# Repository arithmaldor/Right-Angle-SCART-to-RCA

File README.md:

# Copyright and Disclaimer
Copyright: Jacob Proctor 2018

This documentation describes Open Hardware and is licensed under the
CERN OHL v. 1.2.

You may redistribute and modify this documentation under the terms of the
CERN OHL v.1.2. (http://ohwr.org/cernohl). This documentation is distributed
WITHOUT ANY EXPRESS OR IMPLIED WARRANTY, INCLUDING OF
MERCHANTABILITY, SATISFACTORY QUALITY AND FITNESS FOR A
PARTICULAR PURPOSE. Please see the CERN OHL v.1.2 for applicable
conditions

# SCART to RCA Board

Untested, use at your own risk. Will update at a later date with more complete info.

# Parts

Right Angle SCART Connector, various kinds

RCA Connector: PJRAS3X2S01 is available on Mouser and Digikey, but the colors are wrong. Here are the ones I used, a bit cheaper per part:

https://www.ebay.com/itm/QTY-10-6-WAY-PCB-FEMALE-RCA-JACKS-GREEN-YELLOW-BLUE-WHITE-RED-RED-RCA-268N1-14/112220720415?var=null

Mounting hole size is M3, can be used with motherboard standoffs for mounting on MDF or acrylic or something else.

Capacitors and resistors are 0805

LM1881 SOIC8 sync stripper

Molex microusb

SPDT switch

# Version 0.1
This board is untested, designed for use with a case.

# OSHPark
https://oshpark.com/shared_projects/LrkBxQQG

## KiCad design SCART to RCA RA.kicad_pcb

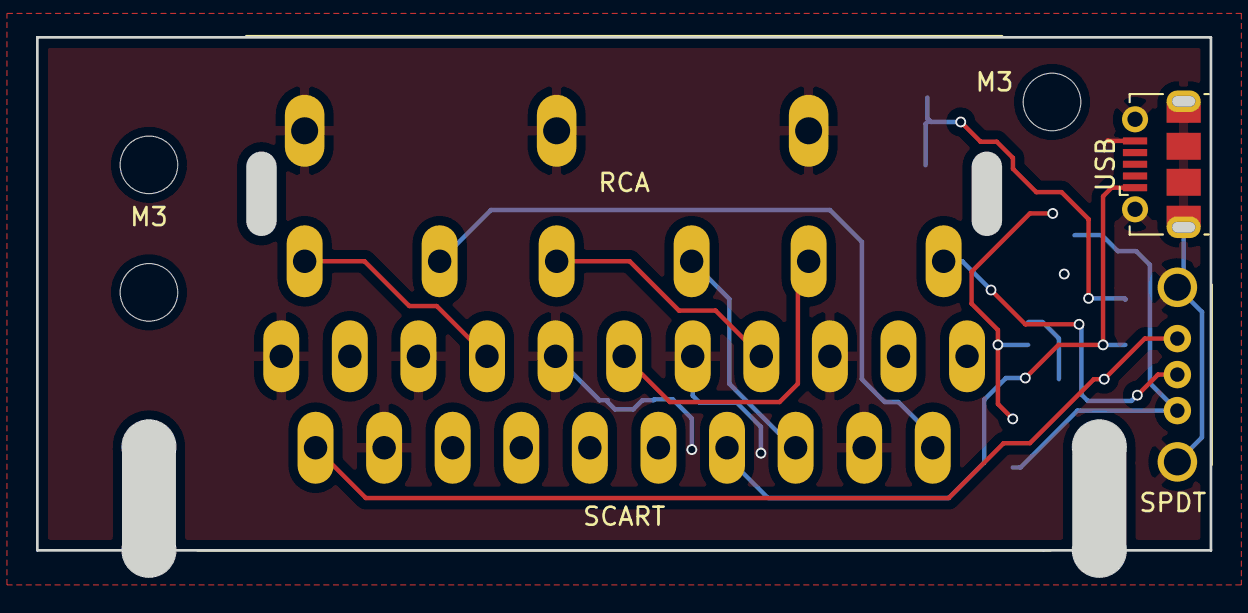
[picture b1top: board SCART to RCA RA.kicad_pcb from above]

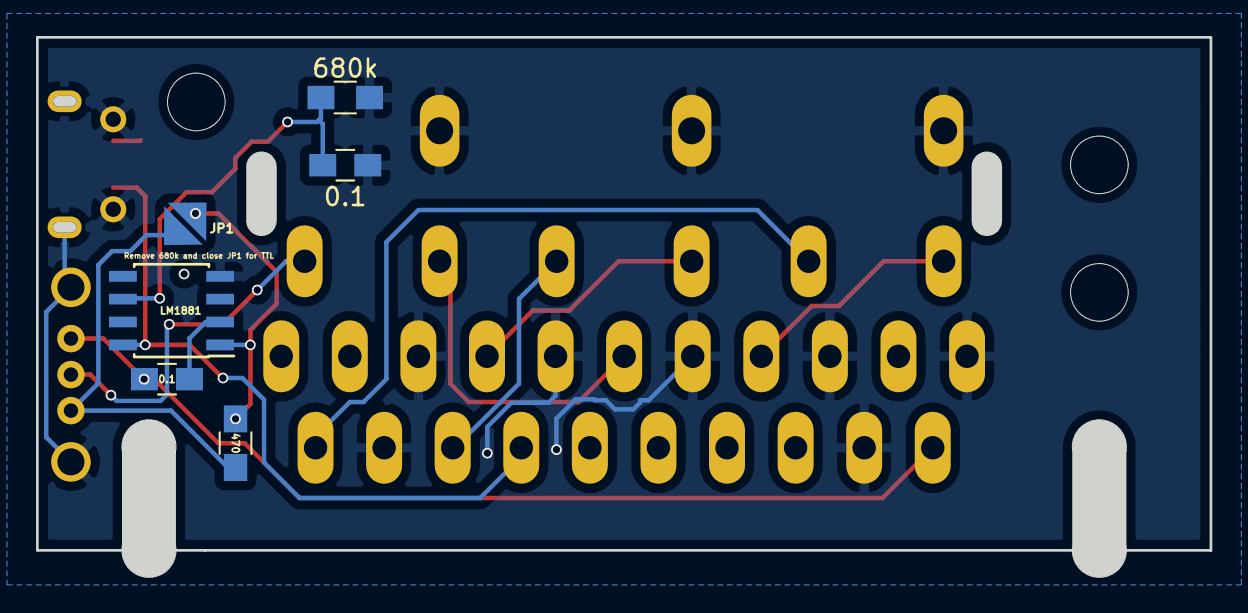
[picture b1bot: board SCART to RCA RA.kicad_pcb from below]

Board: 2 copper layers, 65.2 x 28.5 mm, 13 parts (6 on the bottom side), 13 nets.

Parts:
0.1, 0.1#2: 0.1μF; C_0805_HandSoldering
470: 470Ω; R_0805_HandSoldering
680k: 680kΩ; R_0805_HandSoldering
JP1: J NO; Jumper
LM1881: LM1881; SOIC-8_3.9x4.9mm_Pitch1.27mm
M3, M3#2: M3; MountingHole_3.2mm_M3
RCA: 3x2_RCA
SC2: M3; MountingHole_3.2mm_M3
SCART: SCART-F; SCART-Right-Angle
SPDT: SW_SPDT; SPDT_EG1213
USB: Micro USB; USB_Micro-B_Molex-105017-0001

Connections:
5V: LM1881.8, SCART.8, USB.1
BLUE: RCA.4, SCART.7
CSYNC: RCA.1, SPDT.2
CVBS: 0.1.2, SCART.20, SPDT.3
GND: 0.1#2.1, 680k.1, LM1881.4, RCA.7, RCA.8, RCA.9, SCART.4, SCART.5, SCART.9, SCART.13, SCART.17, SCART.18, SCART.21, SPDT.G, USB.5, USB.6
GREEN: RCA.2, SCART.11
L_AUD: RCA.3, SCART.6
unnamed: 0.1.1, LM1881.2
unnamed: 0.1#2.2, 680k.2, LM1881.6
unnamed: 470.2, JP1.1, SPDT.1
unnamed: 470.1, JP1.2, LM1881.1
RED: RCA.6, SCART.15
R_AUD: RCA.5, SCART.2

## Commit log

2018-06-11 0.1
    Initial revision, meant to be in a custom case. Waiting on feedback from case designer and then will make a test run.
